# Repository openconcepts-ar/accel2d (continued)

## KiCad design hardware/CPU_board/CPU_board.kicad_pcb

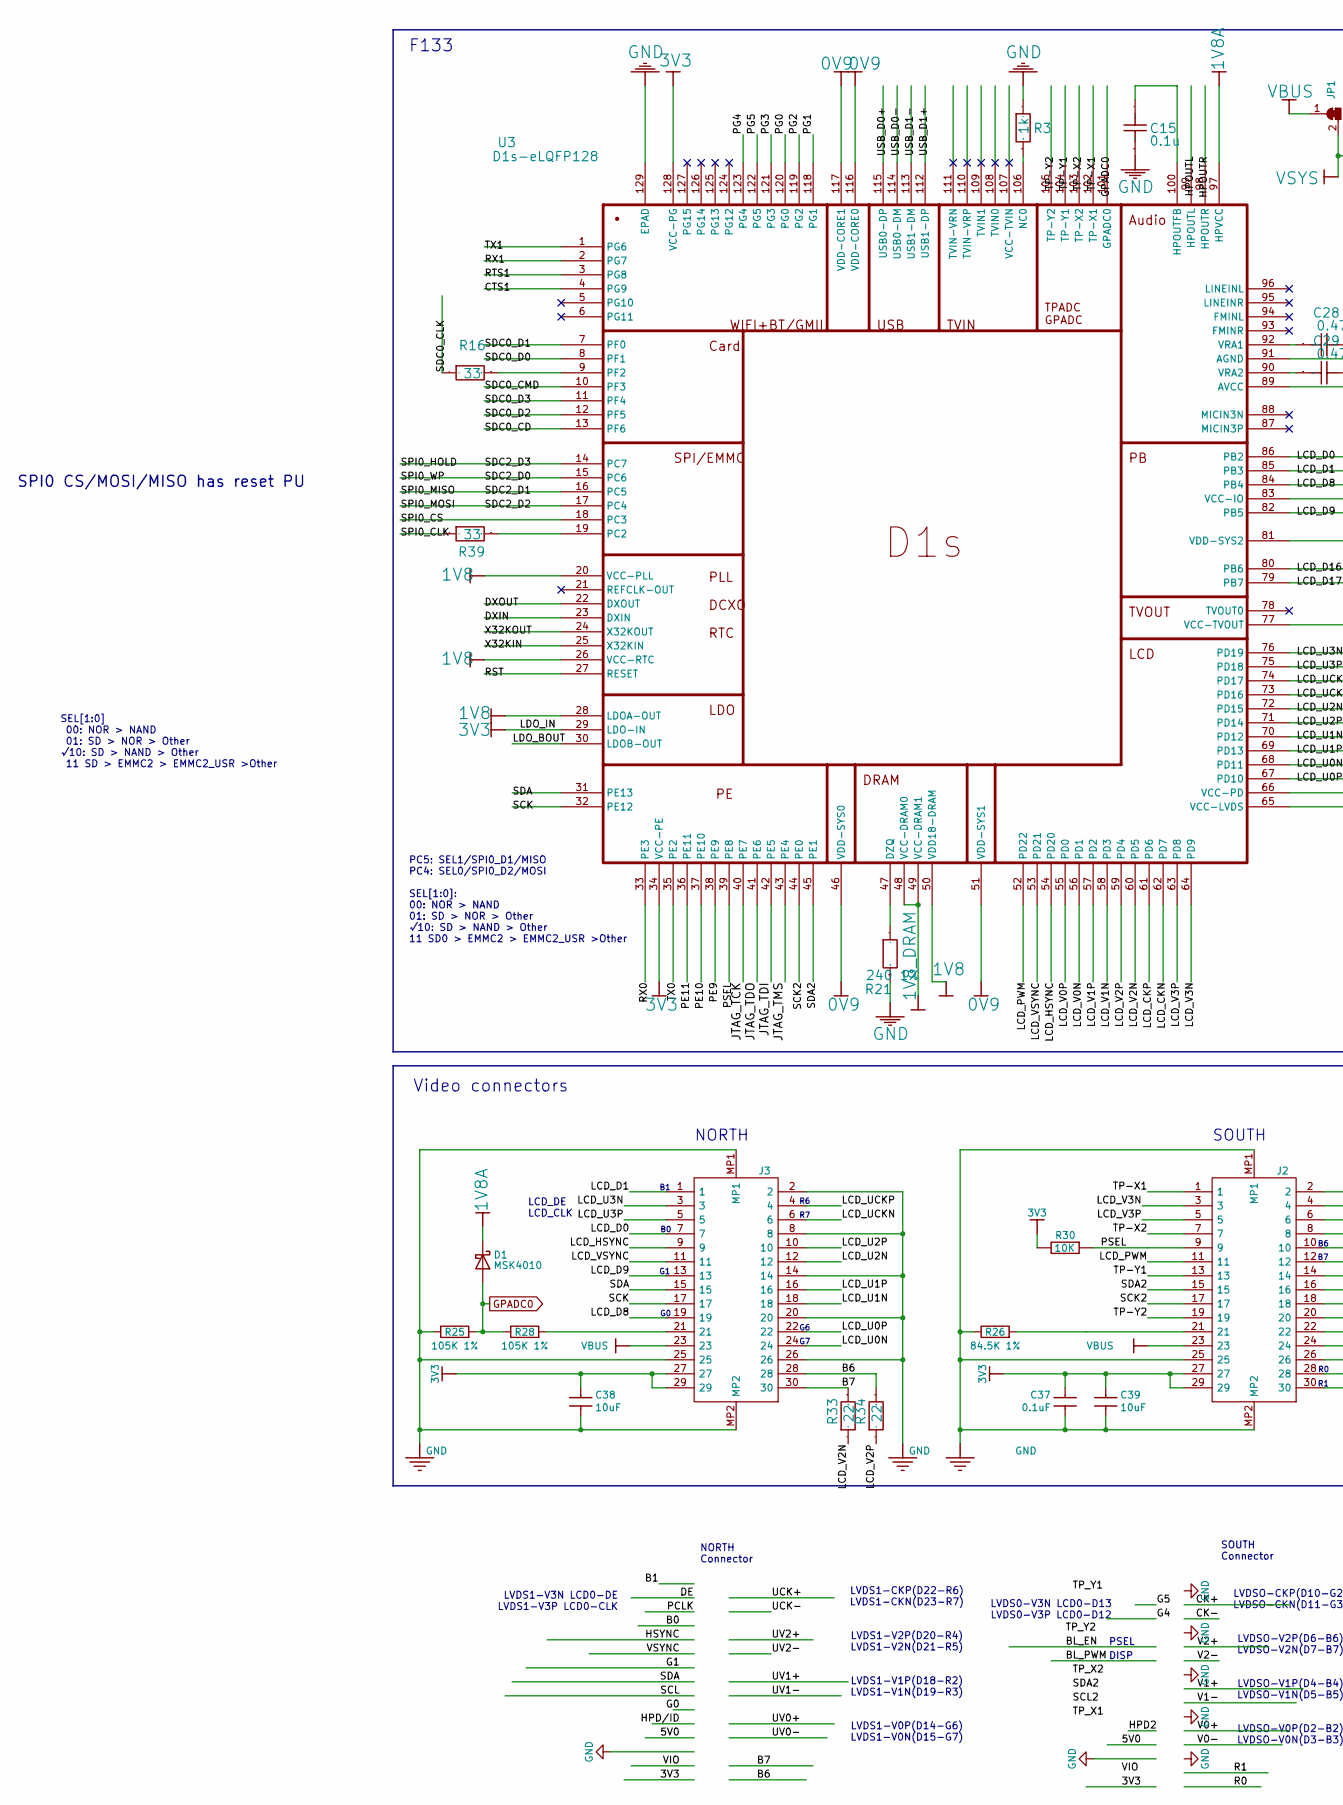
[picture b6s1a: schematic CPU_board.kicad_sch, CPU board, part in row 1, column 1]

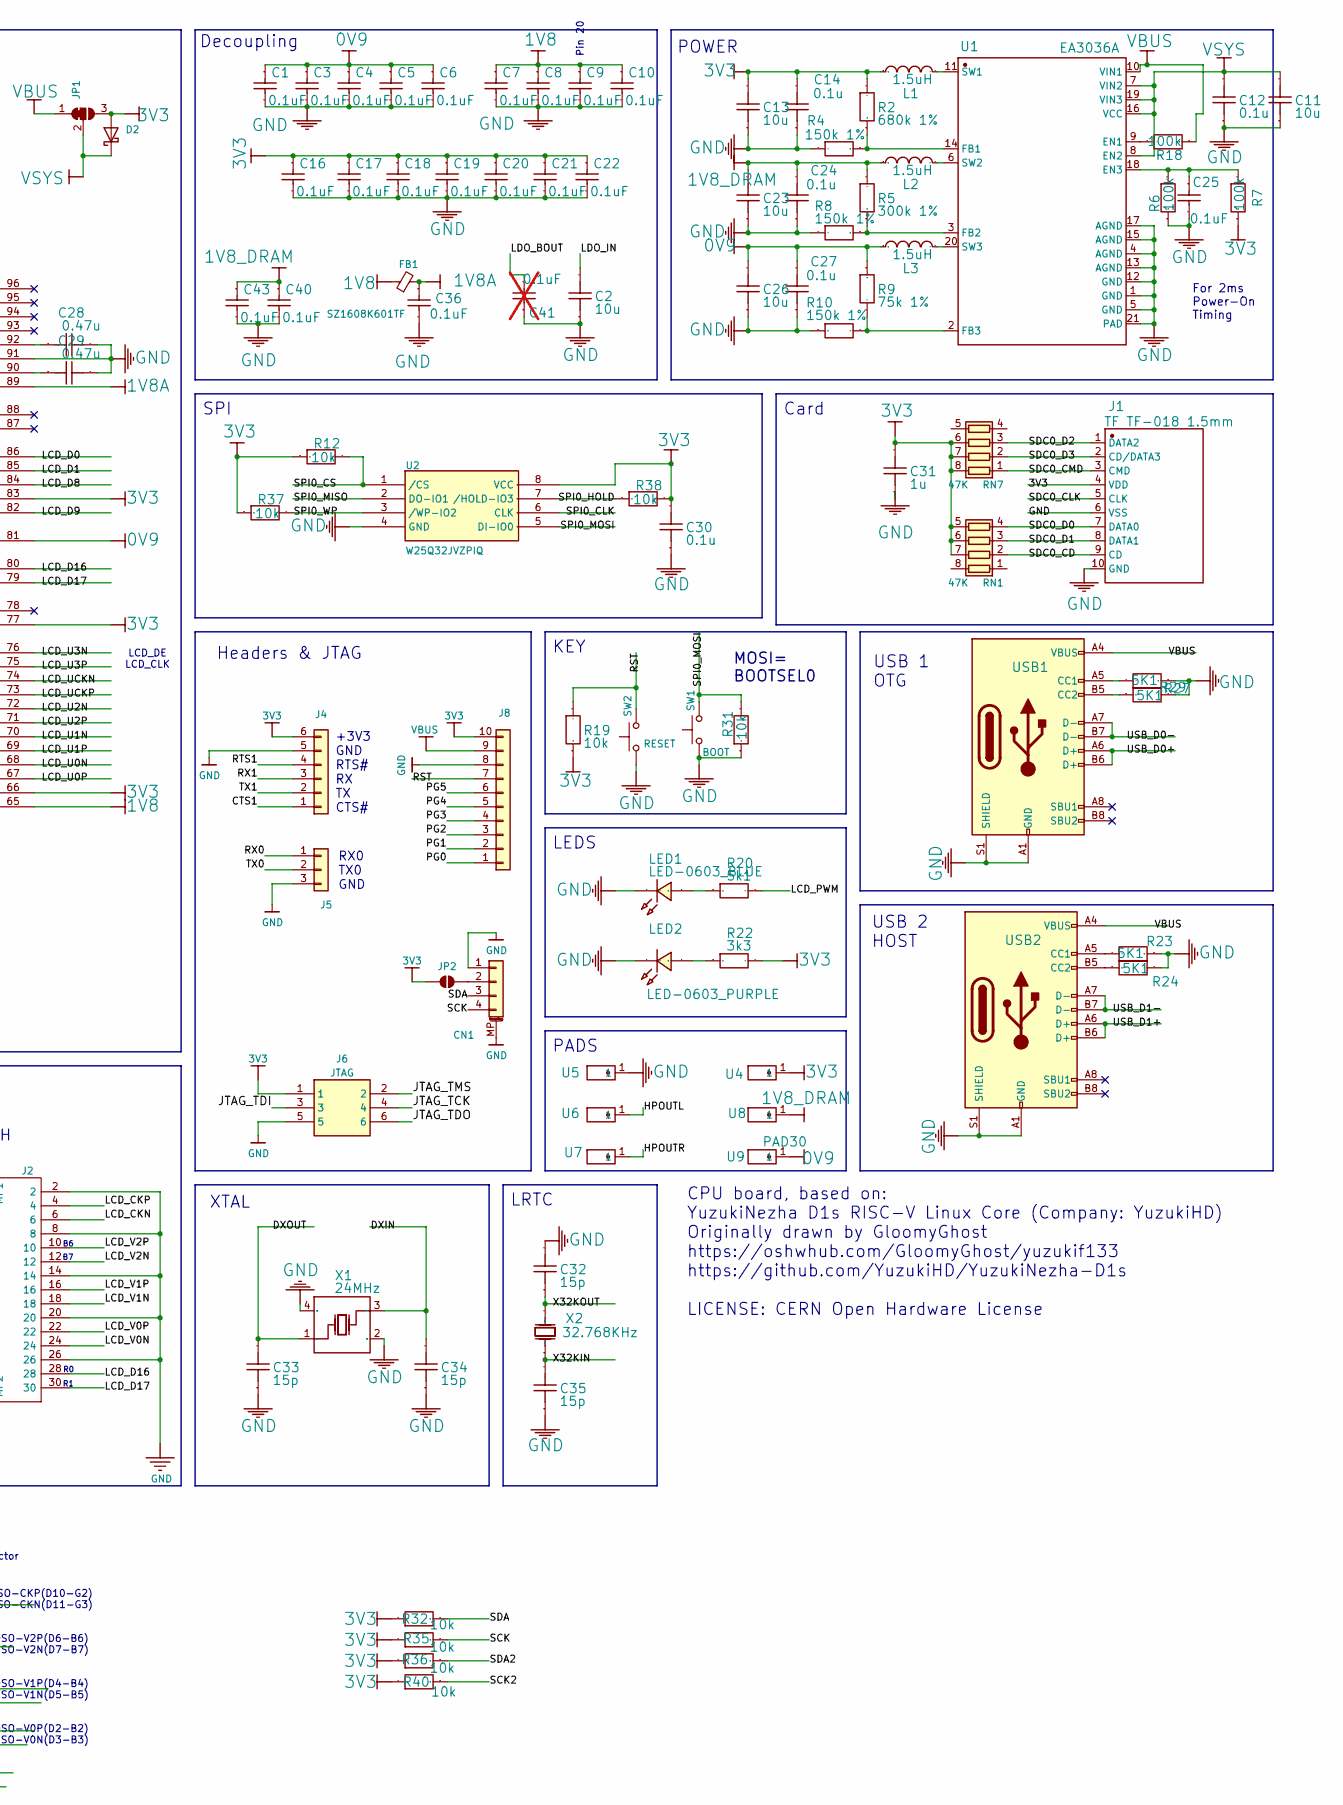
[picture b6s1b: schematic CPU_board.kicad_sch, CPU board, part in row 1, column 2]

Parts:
C1, C3, C4, C5, C6, C7, C8, C9, C10, C16, C17, C18, C19, C20, C21, C22, C25, C36, C40, C43: 0.1uF; C_0402_1005Metric; MPN CL05A104KA5NNNC; LCSC Part Number C100072
C2, C11, C13, C23, C26: 10u; C_0603_1608Metric
C12: 0.1u; C_0402_1005Metric
C14, C24, C27: 0.1u; C_0603_1608Metric
C15, C30: 0.1u; C_0402_1005Metric; MPN CL05A104KA5NNNC; LCSC Part Number C100072
C28, C29: 0.47u; C_0402_1005Metric
C31: 1u; C_0402_1005Metric
C32, C33, C34, C35: 15p; C_0402_1005Metric
C37: 0.1uF; C_0402_1005Metric; LCSC Part Number C60474
C38, C39: 10uF; C_0402_1005Metric; LCSC Part Number C315248
C41: 0.1uF; C_0402_1005Metric; MPN CL05A104KA5NNNC; LCSC Part Number C100072; not fitted
CN1: BM04B-SRSS-TB; JST_SH_BM04B-SRSS-TB_1x04-1MP_P1.00mm_Vertical; MPN BM04B-SRSS-TB(LF)(SN); LCSC Part Number C160390
D1: MSK4010; D_SOD-523; LCSC Part Number C345958
D2: D_Schottky; U-DFN1608-2_L1.6-W0.8-RD; MPN LMBR4020H3T5G
FB1: SZ1608K601TF; L_0603_1608Metric; LCSC Part Number C96991
J1: TF TF-018 1.5mm; TF-SMD_TF-018; MPN TF-018
J2: SOUTH; DF12NB3030DP05V51; MPN DF12NB(3.0)-30DS-0.5V(51)
J3: NORTH; DF12NB3030DP05V51; MPN DF12NB(3.0)-30DS-0.5V(51)
J4: Conn_01x6_Male; PinHeader_1x06_P2.54mm_Vertical
J5: Conn_01x03; PinHeader_1x03_P2.54mm_Vertical
J6: JTAG; Tag-Connect_TC2030-IDC-NL_2x03_P1.27mm_Vertical
J8: Conn_01x10_Male; PinHeader_1x10_P2.54mm_Vertical
JP1: SolderJumper_3_Bridged12; SolderJumper-3_P1.3mm_Bridged12_RoundedPad1.0x1.5mm
JP2: SolderJumper_2_Open; SolderJumper-2_P1.3mm_Open_RoundedPad1.0x1.5mm
L1, L2, L3: 1.5uH; L_Cenker_CKCS201610; MPN CKCS201610-2.2uH/M-N; LCSC Part Number C354533
LED1: LED-0603_BLUE; LED_0603_1608Metric; MPN NCD0603B5; LCSC Part Number C7429915
LED2: LED-0603_PURPLE; LED_0603_1608Metric; MPN XL-1608UVC-04; LCSC Part Number C7371898
R2: 680k 1%; R_0402_1005Metric
R3: 1k; R_0402_1005Metric
R4, R8, R10: 150k 1%; R_0402_1005Metric
R5: 300k 1%; R_0402_1005Metric
R6, R7, R18: 100k; R_0402_1005Metric
R9: 75k 1%; R_0402_1005Metric
R12, R19, R31, R32, R35, R36, R37, R38, R40: 10k; R_0402_1005Metric
R16, R39: 33; R_0402_1005Metric
R20: 5k1; R_0402_1005Metric
R21: 240 1%; R_0402_1005Metric
R22: 3k3; R_0402_1005Metric
R23, R24, R27, R29: 5K1; R_0402_1005Metric
R25, R28: 105K 1%; R_0402_1005Metric; MPN FRC0402F1053TS
R26: 84.5K 1%; R_0402_1005Metric
R30: 10K; R_0402_1005Metric; LCSC Part Number C25531
R33, R34: 22; R_0402_1005Metric
RN1, RN7: 47K; R_Array_Convex_4x0402; MPN 4D02WGJ0473TCE
SW1: BOOT; SW_Push_SPST_NO_Alps_SKRK; MPN SKRKAEE020; LCSC SW0049182
SW2: RESET; SW_Push_SPST_NO_Alps_SKRK; MPN SKRKAEE020; LCSC SW0049182
U1: EA3036A; QFN-20-1EP_3x3mm_P0.4mm_EP1.65x1.65mm; MPN EA3036CQBR
U2: W25Q32JVZPIQ; WSON-8-1EP_6x5mm_P1.27mm_EP3.4x4mm; LCSC Part Number C571260
U3: D1s-eLQFP128; TQFP-128_14x14mm_P0.4mm_with_GND_pad; MPN D1s; LCSC Part Number C5365285
U4, U5, U6, U7, U8, U9: PAD30; TestPoint_Pad_D1.0mm
USB1, USB2: USB_C_Receptacle_G-Switch_GT-USB-7010ASV; MPN GT-USB-7010ASV
X1: 24MHz; Crystal_SMD_2016-4Pin_2.0x1.6mm; MPN TAXM24M4ZDBCCT2T; LCSC Part Number C388793
X2: 32.768KHz; Crystal_SMD_3215-2Pin_3.2x1.5mm; MPN DST310S 32.768KHz; LCSC Part Number C93232

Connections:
0V9: C1.1, C3.1, C4.1, C5.1, C6.1, C26.2, C27.2, L3.1, R9.1, U3.46 (VDD-SYS0), U3.51 (VDD-SYS1), U3.81 (VDD-SYS2), U3.116 (VDD-CORE0), U3.117 (VDD-CORE1), U9.1
1V8: C7.1, C8.1, C9.1, C10.1, FB1.1, U3.20 (VCC-PLL), U3.26 (VCC-RTC), U3.28 (LDOA-OUT), U3.50 (VDD18-DRAM), U3.65 (VCC-LVDS)
1V8A: C36.1, D1.1 (K), FB1.2, U3.89 (AVCC), U3.97 (HPVCC)
1V8_DRAM: C23.2, C24.2, C40.1, C43.1, L2.1, R5.2, U3.48 (VCC-DRAM0), U3.49 (VCC-DRAM1), U8.1
3V3: C2.2, C13.2, C14.2, C16.1, C17.1, C18.1, C19.1, C20.1, C21.1, C22.1, C30.2, C31.2, C37.1, C38.2, C39.2, D2.2 (A), J1.4 (VDD), J2.27, J2.29, J3.27, J3.29, J4.6, J6.1, J8.10, JP1.3 (B), JP2.1 (A), L1.1, R2.2, R7.1, R12.1, R19.1, R22.2, R30.2, R32.2, R35.2, R36.2, R37.1, R38.2, R40.2, RN1.5 (R4.2), RN1.6 (R3.2), RN1.7 (R2.2), RN7.6 (R3.2), RN7.7 (R2.2), RN7.8 (R1.2), U2.8 (VCC), U3.29 (LDO-IN), U3.34 (VCC-PE), U3.66 (VCC-PD), U3.77 (VCC-TVOUT), U3.83 (VCC-IO), U3.128 (VCC-PG), U4.1
/B6: J3.28, R34.1
/B7: J3.30, R33.1
/CTS1: J4.1, U3.4 (PG9)
/DXIN: C34.2, U3.23 (DXIN), X1.3 (OSC2)
/DXOUT: C33.2, U3.22 (DXOUT), X1.1 (OSC1)
/HPOUTL: U3.99 (HPOUTL), U6.1
/HPOUTR: U3.98 (HPOUTR), U7.1
/JTAG_TCK: J6.4, U3.40 (PE7)
/JTAG_TDI: J6.3, U3.42 (PE5)
/JTAG_TDO: J6.6, U3.41 (PE6)
/JTAG_TMS: J6.2, U3.43 (PE4)
/LCD_CKN: J2.6, U3.62 (PD7)
/LCD_CKP: J2.4, U3.61 (PD6)
/LCD_D0: J3.7, U3.86 (PB2)
/LCD_D1: J3.1, U3.85 (PB3)
/LCD_D8: J3.19, U3.84 (PB4)
/LCD_D9: J3.13, U3.82 (PB5)
/LCD_D16: J2.28, U3.80 (PB6)
/LCD_D17: J2.30, U3.79 (PB7)
/LCD_HSYNC: J3.9, U3.54 (PD20)
/LCD_PWM: J2.11, R20.2, U3.52 (PD22)
/LCD_U0N: J3.24, U3.68 (PD11)
/LCD_U0P: J3.22, U3.67 (PD10)
/LCD_U1N: J3.18, U3.70 (PD12)
/LCD_U1P: J3.16, U3.69 (PD13)
/LCD_U2N: J3.12, U3.72 (PD15)
/LCD_U2P: J3.10, U3.71 (PD14)
/LCD_U3N: J3.3, U3.76 (PD19)
/LCD_U3P: J3.5, U3.75 (PD18)
/LCD_UCKN: J3.6, U3.74 (PD17)
/LCD_UCKP: J3.4, U3.73 (PD16)
/LCD_V0N: J2.24, U3.56 (PD1)
/LCD_V0P: J2.22, U3.55 (PD0)
/LCD_V1N: J2.18, U3.58 (PD3)
/LCD_V1P: J2.16, U3.57 (PD2)
/LCD_V2N: J2.12, R33.2, U3.60 (PD5)
/LCD_V2P: J2.10, R34.2, U3.59 (PD4)
/LCD_V3N: J2.3, U3.64 (PD9)
/LCD_V3P: J2.5, U3.63 (PD8)
/LCD_VSYNC: J3.11, U3.53 (PD21)
/LDO_BOUT: C41.2, U3.30 (LDOB-OUT)
/PE9: U3.38 (PE9)
/PE10: U3.37 (PE10)
/PE11: U3.36 (PE11)
/PG0: J8.1, U3.120 (PG0)
/PG1: J8.2, U3.118 (PG1)
/PG2: J8.3, U3.119 (PG2)
/PG3: J8.4, U3.121 (PG3)
/PG4: J8.5, U3.123 (PG4)
/PG5: J8.6, U3.122 (PG5)
/PSEL: J2.9, R30.1, U3.39 (PE8)
/RST: J8.7, R19.2, SW2.1, U3.27 (RESET)
/RTS1: J4.4, U3.3 (PG8)
/RX0: J5.1, U3.33 (PE3)
/RX1: J4.3, U3.2 (PG7)
/SCK: CN1.4, J3.17, R35.1, U3.32 (PE12)
/SCK2: J2.17, R40.1, U3.44 (PE0)
/SDA: CN1.3, J3.15, R32.1, U3.31 (PE13)
/SDA2: J2.15, R36.1, U3.45 (PE1)
/SDC0_CD: J1.9 (CD), RN1.2 (R2.1), U3.13 (PF6)
/SDC0_CLK: J1.5 (CLK), R16.2
/SDC0_CMD: J1.3 (CMD), RN7.1 (R1.1), U3.10 (PF3)
/SDC0_D0: J1.7 (DATA0), RN1.4 (R4.1), U3.8 (PF1)
/SDC0_D1: J1.8 (DATA1), RN1.3 (R3.1), U3.7 (PF0)
/SDC0_D2: J1.1 (DATA2), RN7.3 (R3.1), U3.12 (PF5)
/SDC0_D3: J1.2 (CD/DATA3), RN7.2 (R2.1), U3.11 (PF4)
/SDC2_D0: R37.2, U2.3 (/WP-IO2), U3.15 (PC6)
/SDC2_D1: U2.2 (DO-IO1), U3.16 (PC5)
/SDC2_D2: R31.2, SW1.1, U2.5 (DI-IO0), U3.17 (PC4)
/SDC2_D3: R38.1, U2.7 (/HOLD-IO3), U3.14 (PC7)
/SPI0_CLK: R39.2, U2.6 (CLK)
/SPI0_CS: R12.2, U2.1 (/CS), U3.18 (PC3)
/TP-X1: J2.1, U3.102 (TP-X1)
/TP-X2: J2.7, U3.103 (TP-X2)
/TP-Y1: J2.13, U3.104 (TP-Y1)
/TP-Y2: J2.19, U3.105 (TP-Y2)
/TX0: J5.2, U3.35 (PE2)
/TX1: J4.2, U3.1 (PG6)
/USB_D0+: U3.115 (USB0-DP), USB1.A6 (D+), USB1.B6 (D+)
/USB_D0-: U3.114 (USB0-DM), USB1.A7 (D-), USB1.B7 (D-)
/USB_D1+: U3.112 (USB1-DP), USB2.A6 (D+), USB2.B6 (D+)
/USB_D1-: U3.113 (USB1-DM), USB2.A7 (D-), USB2.B7 (D-)
/X32KIN: C35.2, U3.25 (X32KIN), X2.1 (OSC1)
/X32KOUT: C32.1, U3.24 (X32KOUT), X2.2 (OSC2)
GND: C1.2, C2.1, C3.2, C4.2, C5.2, C6.2, C7.2, C8.2, C9.2, C10.2, C11.1, C12.1, C13.1, C14.1, C15.1, C16.2, C17.2, C18.2, C19.2, C20.2, C21.2, C22.2, C23.1, C24.1, C25.2, C26.1, C27.1, C28.2, C29.2, C30.1, C31.1, C32.2, C33.1, C34.1, C35.1, C36.2, C37.2, C38.1, C39.1, C40.2, C41.1, C43.2, CN1.1, CN1.MP (MountPin), J1.6 (VSS), J1.10 (GND), J2.2, J2.8, J2.14, J2.20, J2.25, J2.26, J2.MP1, J2.MP2, J3.2, J3.8, J3.14, J3.20, J3.25, J3.26, J3.MP1, J3.MP2, J4.5, J5.3, J6.5, J8.8, LED1.2, LED2.2, R3.2, R4.2, R6.1, R8.2, R10.1, R21.1, R23.1, R24.2, R25.1, R26.1, R27.2, R29.1, R31.1, SW1.2, SW2.2, U1.1 (GND), U1.4 (AGND), U1.5 (GND), U1.12 (GND), U1.13 (AGND), U1.15 (AGND), U1.17 (AGND), U1.21 (PAD), U2.4 (GND), U3.91 (AGND), U3.129 (EPAD), U5.1, USB1.A1 (GND), USB1.A12 (GND), USB1.B1 (GND), USB1.B12 (GND), USB1.S1 (SHIELD), USB2.A1 (GND), USB2.A12 (GND), USB2.B1 (GND), USB2.B12 (GND), USB2.S1 (SHIELD), X1.2 (GND), X1.4 (GND)
GPADC0: D1.2 (A), R25.2, R28.1, U3.101 (GPADC0)
unnamed: CN1.2, JP2.2 (B)
unnamed: J2.21, R26.2
unnamed: J3.21, R28.2
unnamed: LED1.1, R20.1
unnamed: LED2.1, R22.1
unnamed: R18.2, U1.9 (EN1)
unnamed: C25.1, R6.2, R7.2, U1.18 (EN3)
unnamed: R2.1, R4.1, U1.14 (FB1)
unnamed: R5.1, R8.1, U1.3 (FB2)
unnamed: R9.2, R10.2, U1.2 (FB3)
unnamed: L1.2, U1.11 (SW1)
unnamed: L2.2, U1.6 (SW2)
unnamed: L3.2, U1.20 (SW3)
unnamed: R21.2, U3.47 (DZQ)
unnamed: C15.2, U3.100 (HPOUTFB)
unnamed: R3.1, U3.106 (NC0)
unnamed: R39.1, U3.19 (PC2)
unnamed: R16.1, U3.9 (PF2)
unnamed: C28.1, U3.92 (VRA1)
unnamed: C29.1, U3.90 (VRA2)
unnamed: R29.2, USB1.A5 (CC1)
unnamed: R27.1, USB1.B5 (CC2)
unnamed: R23.2, USB2.A5 (CC1)
unnamed: R24.1, USB2.B5 (CC2)
VBUS: J2.23, J3.23, J8.9, JP1.1 (A), R18.1, U1.10 (VIN1), USB1.A4 (VBUS), USB1.A9 (VBUS), USB1.B4 (VBUS), USB1.B9 (VBUS), USB2.A4 (VBUS), USB2.A9 (VBUS), USB2.B4 (VBUS), USB2.B9 (VBUS)
VSYS: C11.2, C12.2, D2.1 (K), JP1.2 (C), U1.7 (VIN2), U1.8 (EN2), U1.16 (VCC), U1.19 (VIN3)

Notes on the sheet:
Headers & JTAG
LCD_DE LCD_CLK
PSEL
For 2ms Power-On Timing
Decoupling
LVDSO-CKP(D10-G2) LVDSO-CKN(D11-G3) LVDSO-V2P(D6-B6) LVDSO-V2N(D7-B7) LVDSO-V1P(D4-B4) LVDSO-V1N(D5-B5) LVDSO-V0P(D2-B2) LVDSO-V0N(D3-B3)
NORTH Connector
KEY
CPU board, based on: YuzukiNezha D1s RISC-V Linux Core (Company: YuzukiHD) Originally drawn by GloomyGhost https://oshwhub.com/GloomyGhost/yuzukif133 https://github.com/YuzukiHD/YuzukiNezha-D1s LICENSE: CERN Open Hardware License
POWER
SPI0 CS/MOSI/MISO has reset PU
NORTH
RX0 TX0 GND
DISP
LRTC
LVDS1-CKP(D22-R6) LVDS1-CKN(D23-R7) LVDS1-V2P(D20-R4) LVDS1-V2N(D21-R5) LVDS1-V1P(D18-R2) LVDS1-V1N(D19-R3) LVDS1-V0P(D14-G6) LVDS1-V0N(D15-G7)
SPI
F133
USB 1 OTG
SEL[1:0] 00: NOR > NAND 01: SD > NOR > Other √10: SD > NAND > Other 11 SD > EMMC2 > EMMC2_USR >Other
SOUTH
MOSI= BOOTSEL0
Video connectors
LCD_DE LCD_CLK
LVDS1-V3N LCD0-DE LVDS1-V3P LCD0-CLK
SOUTH Connector
+3V3 GND RTS# RX TX CTS#
Card
LEDS
PC5: SEL1/SPI0_D1/MISO PC4: SEL0/SPI0_D2/MOSI SEL[1:0]: 00: NOR > NAND 01: SD > NOR > Other √10: SD > NAND > Other 11 SD0 > EMMC2 > EMMC2_USR >Other
XTAL
LVDS0-V3N LCD0-D13 LVDS0-V3P LCD0-D12
Pin 20
USB 2 HOST
PADS

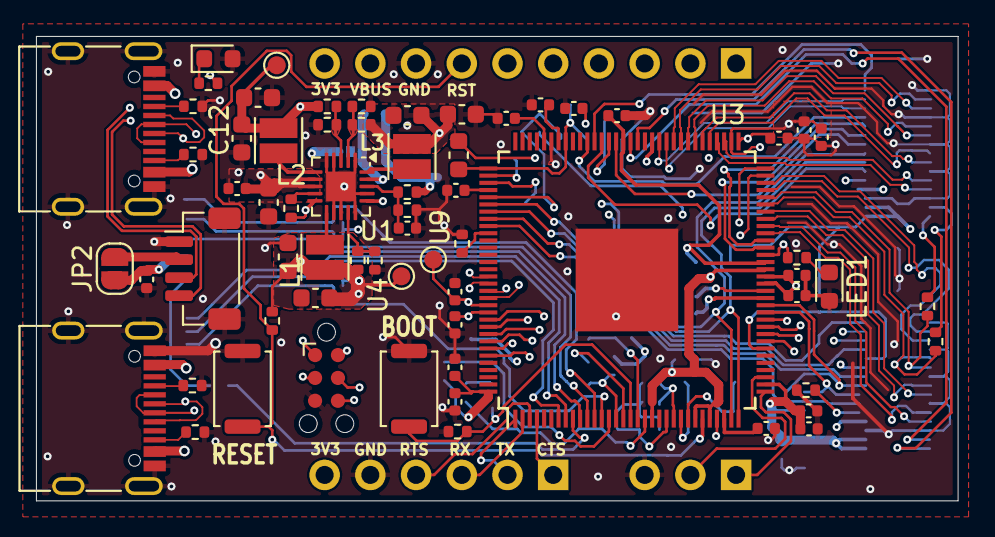
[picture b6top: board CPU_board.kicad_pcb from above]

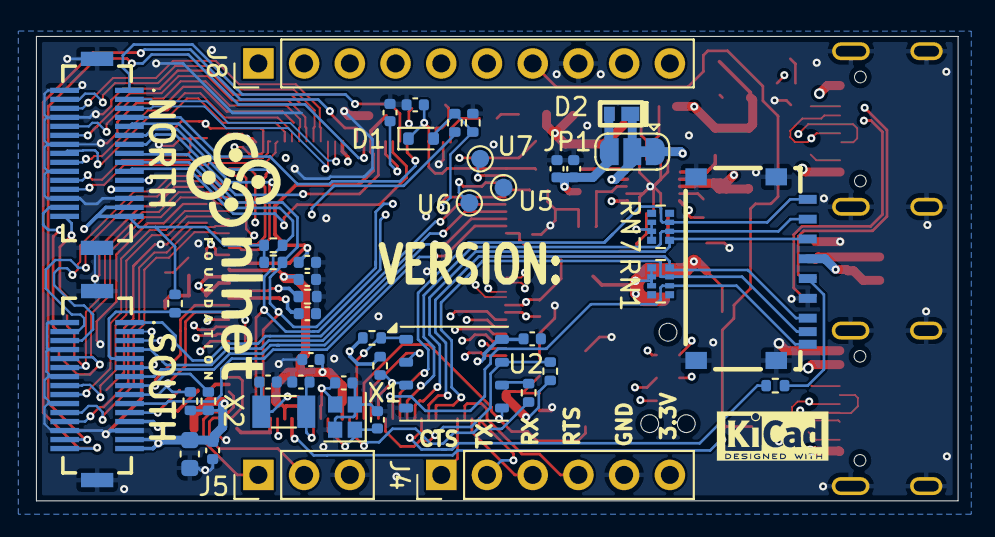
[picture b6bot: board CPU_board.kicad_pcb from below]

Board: 4 copper layers, 51.2 x 25.8 mm, 111 parts (45 on the bottom side), 114 nets.

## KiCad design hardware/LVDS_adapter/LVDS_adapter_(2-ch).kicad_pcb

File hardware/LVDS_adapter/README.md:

## LVDS Adapter 2ch 8-bit with no DC-DC

Tested with the FPGA board and a COTS LVDS to eDP adapter DP_N173HGE (jumper set for 3.3V supply).  
  
BUG FOUND: **the LCD 6-pin power connector had the pins inverted**, providing negative supply to the display. It was solved temporarily by inverting the connection to the 2-pin heeader for external backlight supply.  

It was discovered that the 1366x768 touch enabled display backlight works from 4.5V.

## LVDS without eDP
  
13.3" and 15.6" tested, also the backlight works down to 4.5V.

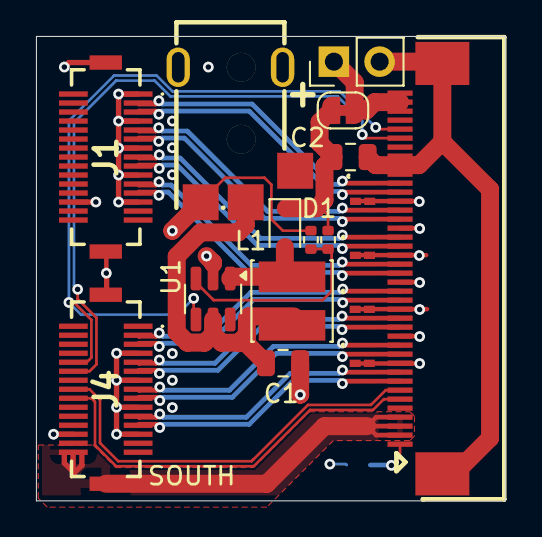
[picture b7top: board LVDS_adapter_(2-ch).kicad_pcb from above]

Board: 4 copper layers, 26.0 x 25.8 mm, 18 parts (1 on the bottom side), 29 nets.

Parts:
C1, C2: 10uF 25V; C_0805_2012Metric
CR1, CR2, CR3, CR4: ESD7004MUTAG; UDFN10_517BB_ONS-L
D1: 1N5819WS; D_SOD-323
J1, J4: DF12NB(3.0)-30DS-0.5V(51); DF12NB3030DP05V51
J2: LVDS; FPC-SMD_40P-P0.50_L4.4-W25.6
J3: BL_POWER; PinHeader_1x02_P2.54mm_Vertical
J5: Barrel_Jack_MountingPin; DC-IN-SMD_DC-045A-13A
JP1: SolderJumper_2_Open; SolderJumper-2_P1.3mm_Open_RoundedPad1.0x1.5mm
JP3: SolderJumper_2_Bridged; SolderJumper-2_P1.3mm_Bridged_RoundedPad1.0x1.5mm
L1: 22uH; L_Cenker_CKCS4020
R2: 8.06K 1%; R_0402_1005Metric
R3: 150K 1%; R_0402_1005Metric
U1: MT3608; SOT-23-6

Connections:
+5V: C1.1, J5.1, L1.1, U1.5 (IN)
/BL_EN: J2.36, J4.10 (9), U1.4 (EN)
/BL_PWM: J2.35, J4.12 (11)
GND: CR1.3, CR1.8, CR2.3, CR2.8, CR3.3, CR3.8, CR4.3, CR4.8, J1.1 (2), J1.7 (8), J1.13 (14), J1.19 (20), J1.25 (26), J1.26 (25), J1.MP1, J1.MP2, J2.10, J2.13, J2.16, J2.19, J2.22, J2.25, J2.28, J4.7 (8), J4.13 (14), J4.19 (20), J4.25 (26), J4.26 (25), J4.MP1, JP1.1 (A)
LED_GND: C1.2, C2.2, J2.31, J2.32, J2.33, J2.MP (MountPin), J3.2, J5.2, R2.2, U1.2 (GND)
LED_VCC: J2.38, J2.39, J2.40, J3.1, JP3.2 (B)
LVDS_E0_N: CR2.5, CR2.6, J1.23 (24), J2.20
LVDS_E0_P: CR2.4, CR2.7, J1.21 (22), J2.21
LVDS_E1_N: CR2.2, CR2.9, J1.17 (18), J2.23
LVDS_E1_P: CR2.1, CR2.10, J1.15 (16), J2.24
LVDS_E2_N: CR1.5, CR1.6, J1.11 (12), J2.26
LVDS_E2_P: CR1.4, CR1.7, J1.9 (10), J2.27
LVDS_EC_N: CR1.2, CR1.9, J1.5 (6), J2.29
LVDS_EC_P: CR1.1, CR1.10, J1.3 (4), J2.30
LVDS_O0_N: CR4.5, CR4.6, J2.8, J4.23 (24)
LVDS_O0_P: CR4.4, CR4.7, J2.9, J4.21 (22)
LVDS_O1_N: CR4.2, CR4.9, J2.11, J4.17 (18)
LVDS_O1_P: CR4.1, CR4.10, J2.12, J4.15 (16)
LVDS_O2_N: CR3.5, CR3.6, J2.14, J4.11 (12)
LVDS_O2_P: CR3.4, CR3.7, J2.15, J4.9 (10)
LVDS_OC_N: CR3.2, CR3.9, J2.17, J4.5 (6)
LVDS_OC_P: CR3.1, CR3.10, J2.18, J4.3 (4)
unnamed: D1.2 (A), L1.2, U1.1 (SW)
unnamed: C2.1, D1.1 (K), JP3.1 (A), R3.2
unnamed: J2.1, JP1.2 (B)
unnamed: R2.1, R3.1, U1.3 (FB)
SCL2: J2.6, J4.18 (17)
SDA2: J2.7, J4.16 (15)
VCC: J2.2, J2.3, J2.4, J4.30 (29), J4.MP2

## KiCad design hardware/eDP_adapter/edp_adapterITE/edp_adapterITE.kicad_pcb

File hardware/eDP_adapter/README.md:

# LVDS to eDP

## Build
In a first terminal:
```
$ python3 ./gsd_orangecrab.py --with-gpio --pixel-bus-width=32 --timer-uptime --cpu-type=vexriscv --uart-baudrate 921600 --sys-clk-freq 75e6
```

In a second terminal:
```
$ cd micropython/ports/litex
$ make BUILD_DIRECTORY=../../../build/gsd_orangecrab #make sure riscv gcc is in PATH
$ litex_term /dev/ttyUSB1 --speed 921600 --kernel=build/firmware.bin
```
This wll launch micropython REPL when bitstream is loaded (use first terminal):

```
$ openFPGALoader -c ft2232 build/gsd_orangecrab/gateware/gsd_orangecrab.bit
```

## Board based on ITE chip

</img>

First terminal:
```
$ python3 micropython/tools/pyboard.py -d /dev/ttyUSB1 -b 921600 demos/micropython/i2c_it6251_test.py
```
(Or paste in the micropython REPL with Ctrl-E if script size is an issue)  
This activates the LVDS to eDP conversion and produces at the console:

```
Screen size: 34 x 19cm
Native resolutions:
	1366 x  768	71.1 MHz pixel clock
	1366 x  768	60.2 MHz pixel clock
reg0E = 90, Link Rate = HBR
reg0D = 3e,  HPD Video Stable
frequency = 34302729, xCnt = 806
Data Enable start: (71, 8)
The following is the current Modeline, not from EDID:
Modeline "1366x768@30_0" 34.303 1366 1400 1432 1469 768 772 774 778 +HSync +VSync
```
  
**Which is a truly correct modeline deduced from actual register values of the ITE chip.**

## Smoke test
Step up for backlight outputs about 12V (both under load or if not loaded).  
LDO 1.8V works.  
**ISSUE***: Yhe DC-DC for 3.3V display supply outputs 1.2V since incorrect 100K/100K divider. Corrected by disabling the DC-DC and taking 3.3V from the main board (using the jumper for that purpose, but this is **not recommended** since extra load can influence the main board 3.3V supply and may make DRAM to not pass checks).  
**AUX has polarity inverted** but it was fixed manually on a 40-to-30 eDP adapter.   
As shown above, the I2C communication works (tested with the FPGA board)  

## Board based on NCS chip

Smoke test: do same fixes as in the ITE board
Step up for backlight outputs about 12V (no load). LDO for 1.2V is also ok. 
The I2C communication works (tested with the FPGA board)

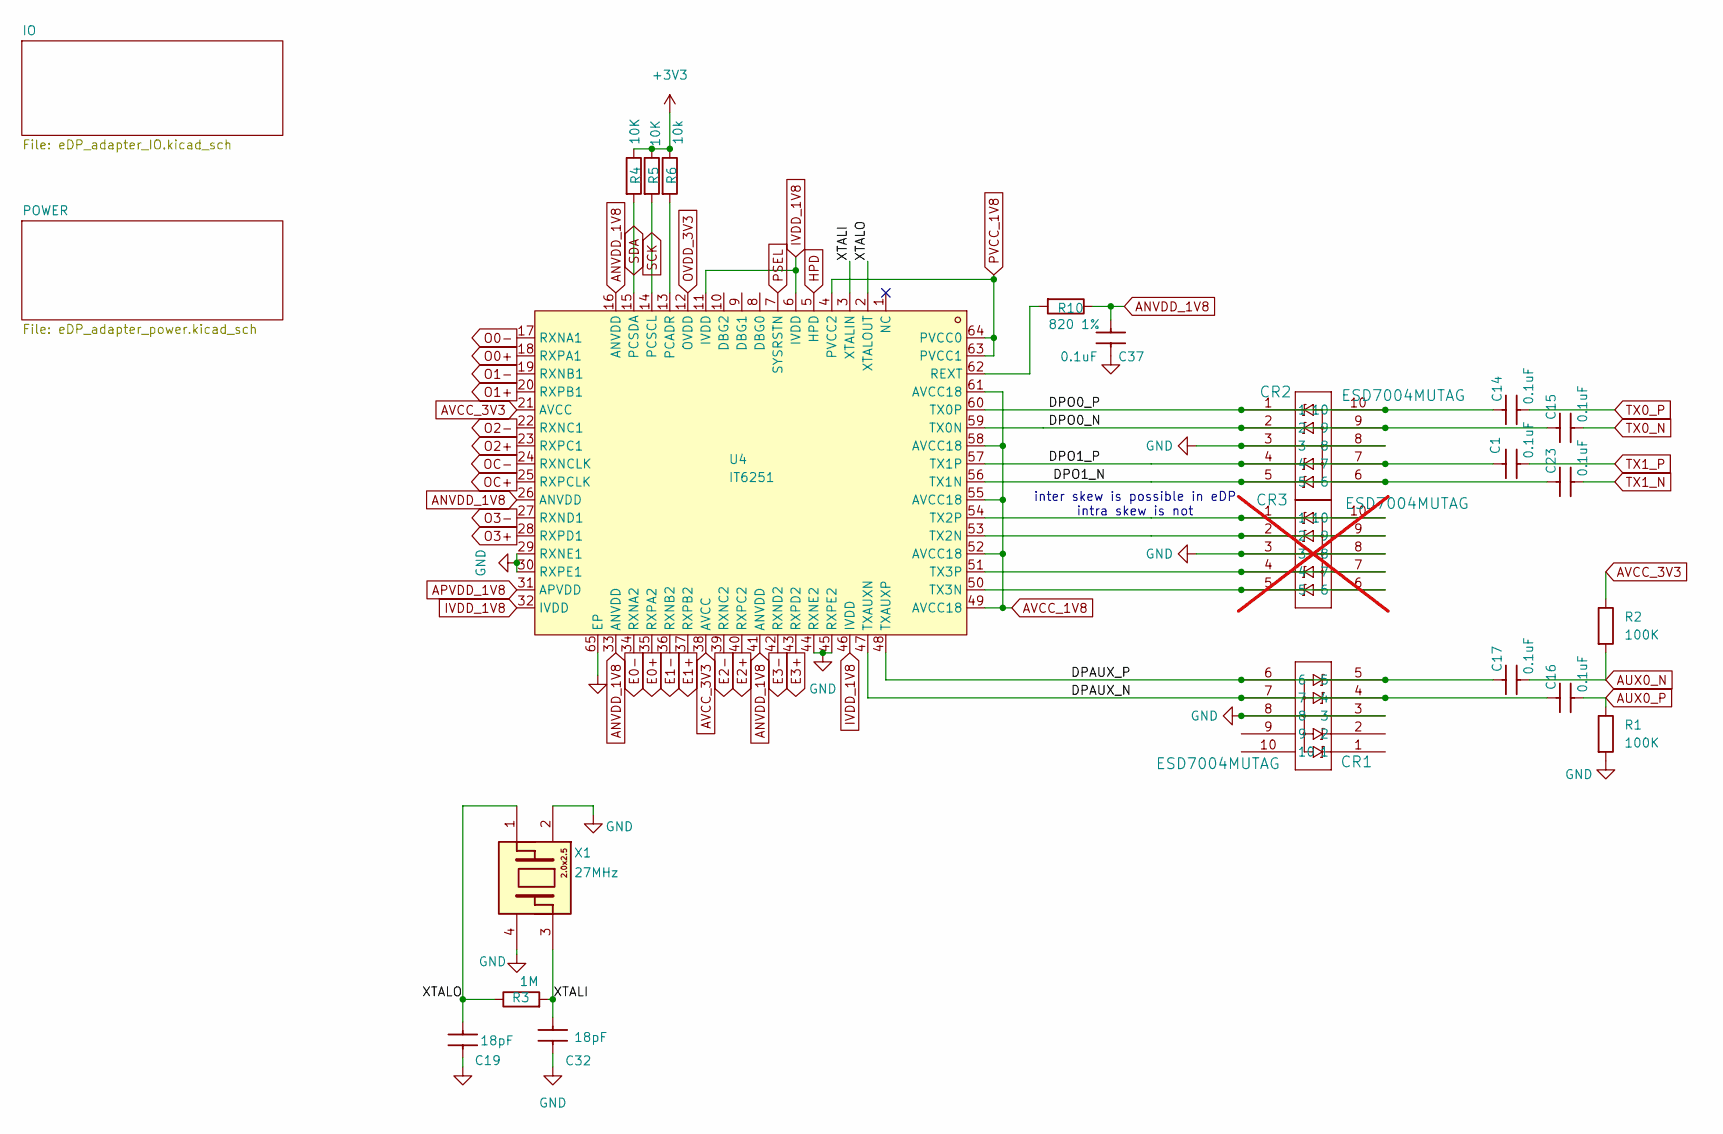
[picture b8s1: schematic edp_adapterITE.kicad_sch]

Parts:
C1, C14, C17, C23: 0.1uF; C_0402_1005Metric
C15, C16, C37: 0.1uF; C_0402_1005Metric; LCSC Part Number C60474
C19, C32: 18pF; C_0402_1005Metric
CR1, CR2: ESD7004MUTAG; UDFN10_517BB_ONS-L; LCSC Part Number C2931115
CR3: ESD7004MUTAG; UDFN10_517BB_ONS-L; LCSC Part Number C2931115; not fitted
R1, R2: 100K; R_0402_1005Metric
R3: 1M; R_0402_1005Metric
R4, R5: 10K; R_0402_1005Metric
R6: 10k; R_0402_1005Metric
R10: 820 1%; R_0402_1005Metric
U4: IT6251; QFN-64_L9.0-W9.0-P0.50-BL-EP3.8; MPN IT6251; LCSC Part C9900011361
X1: 27MHz; Crystal_SMD_2520-4Pin_2.5x2.0mm; MPN X252027MOB4SI; LCSC Part Number C371132

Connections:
+3V3: R4.1, R5.1, R6.1; also elsewhere on the board
/DPAUX_N: C16.1, CR1.4, CR1.7, U4.47 (TXAUXN)
/DPAUX_P: C17.1, CR1.5, CR1.6, U4.48 (TXAUXP)
/DPO0_N: C15.1, CR2.2, CR2.9, U4.59 (TX0N)
/DPO0_P: C14.1, CR2.1, CR2.10, U4.60 (TX0P)
/DPO1_N: C23.1, CR2.5, CR2.6, U4.56 (TX1N)
/DPO1_P: C1.1, CR2.4, CR2.7, U4.57 (TX1P)
/XTALI: C32.2, R3.2, U4.3 (XTALIN), X1.3 (X2)
/XTALO: C19.1, R3.1, U4.2 (XTALOUT), X1.1 (X1)
ANVDD_1V8: C37.2, R10.1, U4.16 (ANVDD), U4.26 (ANVDD), U4.33 (ANVDD), U4.41 (ANVDD), U4.49 (AVCC18), U4.52 (AVCC18), U4.55 (AVCC18), U4.58 (AVCC18), U4.61 (AVCC18); also elsewhere on the board
APVDD_1V8: U4.4 (PVCC2), U4.31 (APVDD), U4.63 (PVCC1), U4.64 (PVCC0); also elsewhere on the board
AUX0_N: C17.2, R2.2; also elsewhere on the board
AUX0_P: C16.2, R1.1; also elsewhere on the board
AVCC_3V3: R2.1, U4.12 (OVDD), U4.21 (AVCC), U4.38 (AVCC); also elsewhere on the board
E0+: U4.35 (RXPA2); also elsewhere on the board
E0-: U4.34 (RXNA2); also elsewhere on the board
E1+: U4.37 (RXPB2); also elsewhere on the board
E1-: U4.36 (RXNB2); also elsewhere on the board
E2+: U4.40 (RXPC2); also elsewhere on the board
E2-: U4.39 (RXNC2); also elsewhere on the board
E3+: U4.43 (RXPD2); also elsewhere on the board
E3-: U4.42 (RXND2); also elsewhere on the board
GND: C19.2, C32.1, C37.1, CR1.3, CR1.8, CR2.3, CR2.8, CR3.3, CR3.8, R1.2, U4.29 (RXNE1), U4.30 (RXPE1), U4.44 (RXNE2), U4.45 (RXPE2), U4.65 (EP), X1.2 (NC1), X1.4 (NC2); also elsewhere on the board
HPD: U4.5 (HPD); also elsewhere on the board
IVDD_1V8: U4.6 (IVDD), U4.11 (IVDD), U4.32 (IVDD), U4.46 (IVDD); also elsewhere on the board
unnamed: R6.2, U4.13 (PCADR)
unnamed: R10.2, U4.62 (REXT)
unnamed: CR3.2, CR3.9, U4.53 (TX2N)
unnamed: CR3.1, CR3.10, U4.54 (TX2P)
unnamed: CR3.5, CR3.6, U4.50 (TX3N)
unnamed: CR3.4, CR3.7, U4.51 (TX3P)
O0+: U4.18 (RXPA1); also elsewhere on the board
O0-: U4.17 (RXNA1); also elsewhere on the board
O1+: U4.20 (RXPB1); also elsewhere on the board
O1-: U4.19 (RXNB1); also elsewhere on the board
O2+: U4.23 (RXPC1); also elsewhere on the board
O2-: U4.22 (RXNC1); also elsewhere on the board
O3+: U4.28 (RXPD1); also elsewhere on the board
O3-: U4.27 (RXND1); also elsewhere on the board
OC+: U4.25 (RXPCLK); also elsewhere on the board
OC-: U4.24 (RXNCLK); also elsewhere on the board
PSEL: U4.7 (SYSRSTN); also elsewhere on the board
SCK: R5.2, U4.14 (PCSCL); also elsewhere on the board
SDA: R4.2, U4.15 (PCSDA); also elsewhere on the board
TX0_N: C15.2; also elsewhere on the board
TX0_P: C14.2; also elsewhere on the board
TX1_N: C23.2; also elsewhere on the board
TX1_P: C1.2; also elsewhere on the board

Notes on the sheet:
inter skew is possible in eDP intra skew is not

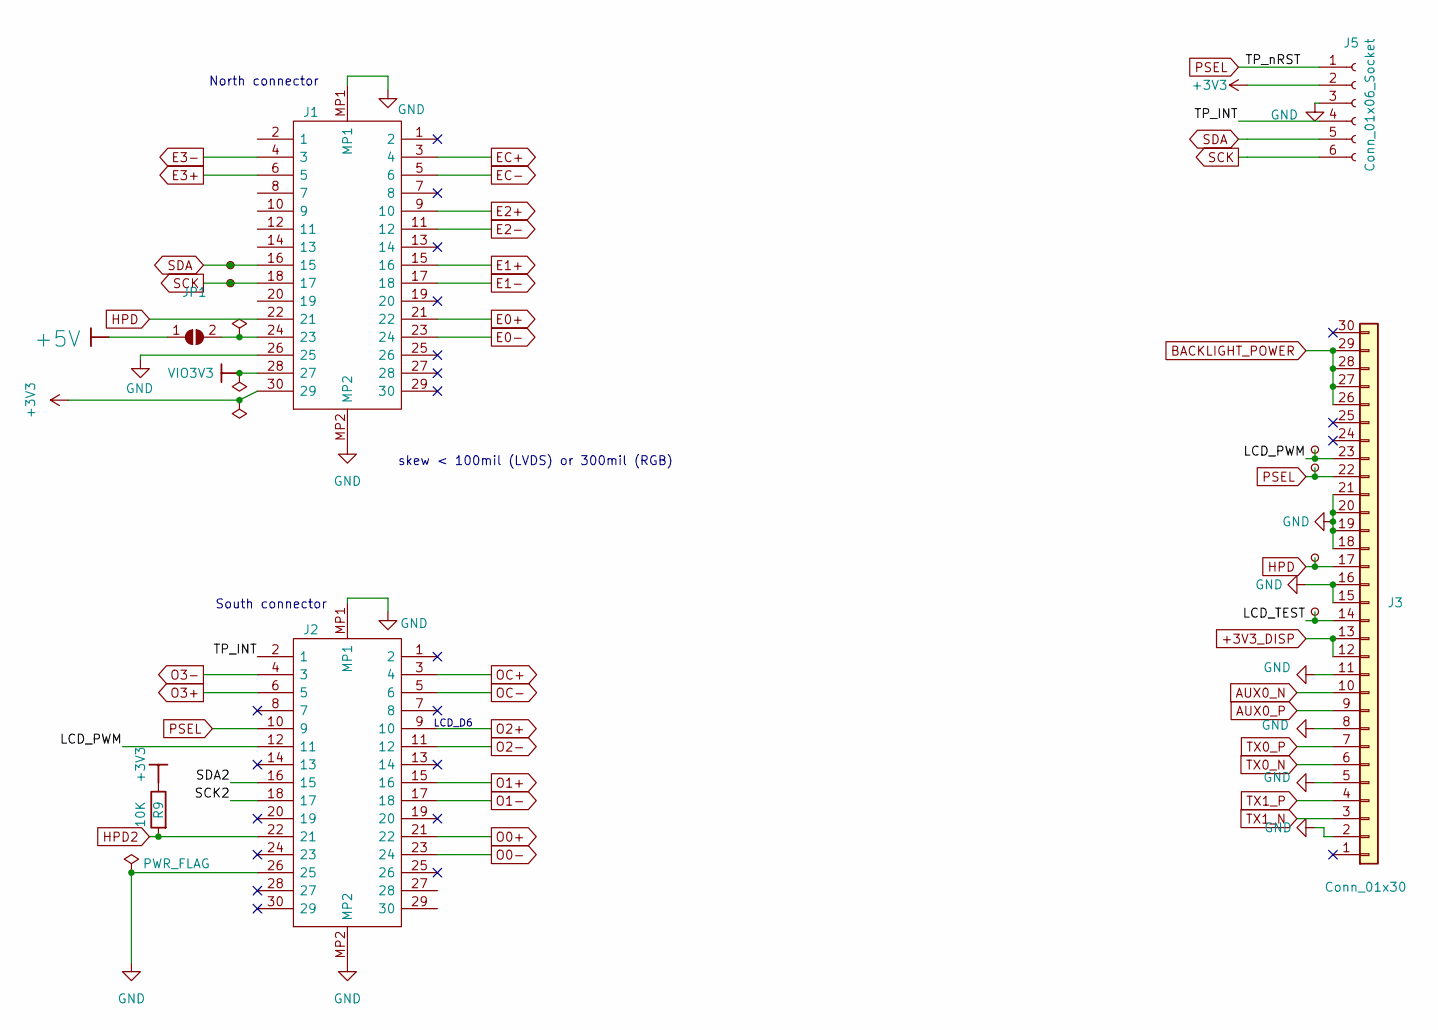
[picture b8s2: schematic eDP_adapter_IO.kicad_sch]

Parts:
J1, J2: DF12NB(3.0)-30DS-0.5V(51); DF12NB3030DP05V51; Manufacturer_Part_Number DF12NB(3.0)-30DP-0.5V(51); LCSC Part Number C2904115
J3: Conn_01x30; FPC-SMD_30P-P0.50_FPC-0.5FX-30PWBH15; MPN FPC-0.5FX-30PWBH15
J5: Conn_01x06_Socket; FPC-SMD_FH52K-6S-0.5SH; MPN FH52K-6S-0.5SH
JP1: SolderJumper_2_Open; SolderJumper-2_P1.3mm_Open_RoundedPad1.0x1.5mm
R9: 10K; R_0402_1005Metric
TP4, TP5, TP6, TP7, TP13, TP14: TestPoint_Small; TestPoint_Pad_D1.0mm

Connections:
+3V3: J1.30 (29), J5.2, R9.1; also elsewhere on the board
+3V3_DISP: J3.12, J3.13; also elsewhere on the board
+5V: JP1.1 (A); also elsewhere on the board
/IO/LCD_PWM: J2.12 (11), J3.23, TP4.1
/IO/LCD_TEST: J3.14, TP7.1
/IO/SCK2: J2.18 (17)
/IO/SDA2: J2.16 (15)
/IO/TP_INT: J2.2 (1), J5.4
AUX0_N: J3.10; also elsewhere on the board
AUX0_P: J3.9; also elsewhere on the board
BACKLIGHT_POWER: J3.26, J3.27, J3.28, J3.29; also elsewhere on the board
E0+: J1.21 (22); also elsewhere on the board
E0-: J1.23 (24); also elsewhere on the board
E1+: J1.15 (16); also elsewhere on the board
E1-: J1.17 (18); also elsewhere on the board
E2+: J1.9 (10); also elsewhere on the board
E2-: J1.11 (12); also elsewhere on the board
E3+: J1.6 (5); also elsewhere on the board
E3-: J1.4 (3); also elsewhere on the board
EC+: J1.3 (4)
EC-: J1.5 (6)
GND: J1.26 (25), J1.MP1, J1.MP2, J2.26 (25), J2.MP1, J2.MP2, J3.2, J3.5, J3.8, J3.11, J3.15, J3.16, J3.18, J3.19, J3.20, J3.21, J3.MP (MountPin), J5.3, J5.MP (MountPin); also elsewhere on the board
HPD: J1.22 (21), J3.17, TP6.1; also elsewhere on the board
HPD2: J2.22 (21), R9.2
unnamed: J1.24 (23), JP1.2 (B)
O0+: J2.21 (22); also elsewhere on the board
O0-: J2.23 (24); also elsewhere on the board
O1+: J2.15 (16); also elsewhere on the board
O1-: J2.17 (18); also elsewhere on the board
O2+: J2.9 (10); also elsewhere on the board
O2-: J2.11 (12); also elsewhere on the board
O3+: J2.6 (5); also elsewhere on the board
O3-: J2.4 (3); also elsewhere on the board
OC+: J2.3 (4); also elsewhere on the board
OC-: J2.5 (6); also elsewhere on the board
PSEL: J2.10 (9), J3.22, J5.1, TP5.1; also elsewhere on the board
SCK: J1.18 (17), J5.6, TP14.1; also elsewhere on the board
SDA: J1.16 (15), J5.5, TP13.1; also elsewhere on the board
TX0_N: J3.6; also elsewhere on the board
TX0_P: J3.7; also elsewhere on the board
TX1_N: J3.3; also elsewhere on the board
TX1_P: J3.4; also elsewhere on the board
VIO3V3: J1.28 (27)

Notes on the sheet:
LCD_D6
skew < 100mil (LVDS) or 300mil (RGB)
South connector
North connector
